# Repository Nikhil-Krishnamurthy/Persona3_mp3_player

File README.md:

# Persona3_mp3_player
A persona 3 style mp3 player with headphone and bluetooth support.

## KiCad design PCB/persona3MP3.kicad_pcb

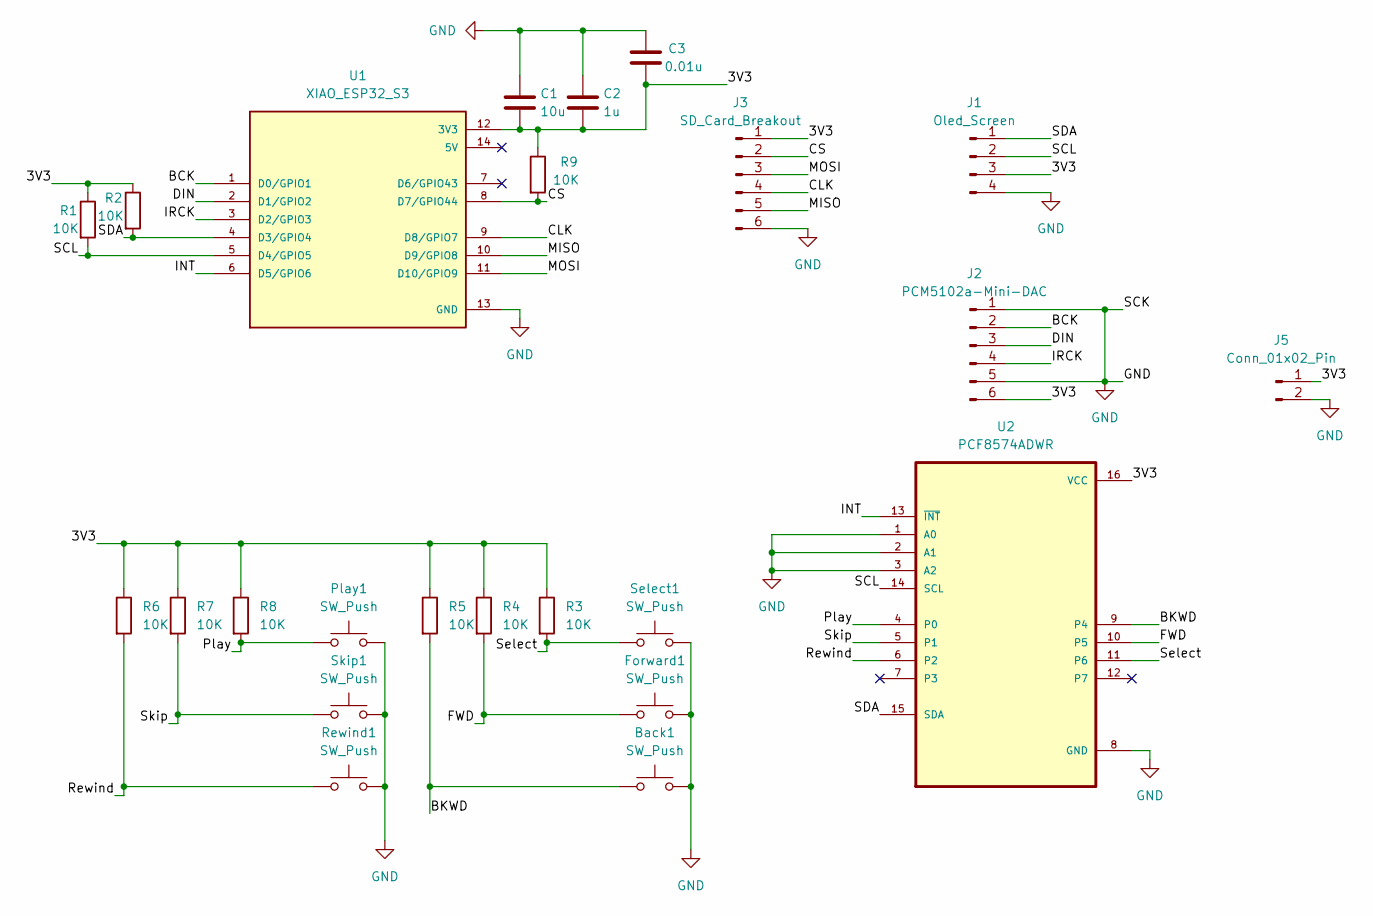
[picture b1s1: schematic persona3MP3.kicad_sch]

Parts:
Back1: SW_Push; PTS645VL392LFS
C1: 10u; C_0805_2012Metric_Pad1.18x1.45mm_HandSolder
C2: 1u; C_0805_2012Metric_Pad1.18x1.45mm_HandSolder
C3: 0.01u; C_0805_2012Metric_Pad1.18x1.45mm_HandSolder
Forward1: SW_Push; PTS645VL392LFS
J1: Oled_Screen; PinHeader_1x04_P2.54mm_Vertical
J2: PCM5102a-Mini-DAC; PinHeader_1x06_P2.54mm_Vertical
J3: SD_Card_Breakout; PinHeader_1x06_P2.54mm_Vertical
J5: Conn_01x02_Pin; PinSocket_1x02_P2.54mm_Vertical
Play1: SW_Push; PTS645VL392LFS
R1, R2, R3, R4, R5, R6, R7, R8, R9: 10K; R_0805_2012Metric_Pad1.20x1.40mm_HandSolder
Rewind1: SW_Push; PTS645VL392LFS
Select1: SW_Push; PTS645VL392LFS
Skip1: SW_Push; PTS645VL392LFS
U1: XIAO_ESP32_S3; MODULE_XIAO_ESP32_S3; PARTREV April 22nd, 2026
U2: PCF8574ADWR; SOIC127P1030X265-16N; DigiKey_Part_Number 296-13105-1-ND

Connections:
/3V3: C1.2, C2.2, C3.2, J1.3, J2.6, J3.1, J5.1, R1.1, R2.1, R3.1, R4.1, R5.1, R6.1, R7.1, R8.1, R9.1, U1.12 (3V3), U2.16 (VCC)
/BCK: J2.2, U1.1 (D0/GPIO1)
/BKWD: Back1.1, R5.2, U2.9 (P4)
/CLK: J3.4, U1.9 (D8/GPIO7)
/CS: J3.2, R9.2, U1.8 (D7/GPIO44)
/DIN: J2.3, U1.2 (D1/GPIO2)
/FWD: Forward1.1, R4.2, U2.10 (P5)
/INT: U1.6 (D5/GPIO6), U2.13 (~INT)
/IRCK: J2.4, U1.3 (D2/GPIO3)
/MISO: J3.5, U1.10 (D9/GPIO8)
/MOSI: J3.3, U1.11 (D10/GPIO9)
/Play: Play1.1, R8.2, U2.4 (P0)
/Rewind: R6.2, Rewind1.1, U2.6 (P2)
/SCL: J1.2, R1.2, U1.5 (D4/GPIO5), U2.14 (SCL)
/SDA: J1.1, R2.2, U1.4 (D3/GPIO4), U2.15 (SDA)
/Select: R3.2, Select1.1, U2.11 (P6)
/Skip: R7.2, Skip1.1, U2.5 (P1)
GND: Back1.2, C1.1, C2.1, C3.1, Forward1.2, J1.4, J2.1, J2.5, J3.6, J5.2, Play1.2, Rewind1.2, Select1.2, Skip1.2, U1.13 (GND), U2.1 (A0), U2.2 (A1), U2.3 (A2), U2.8 (GND)

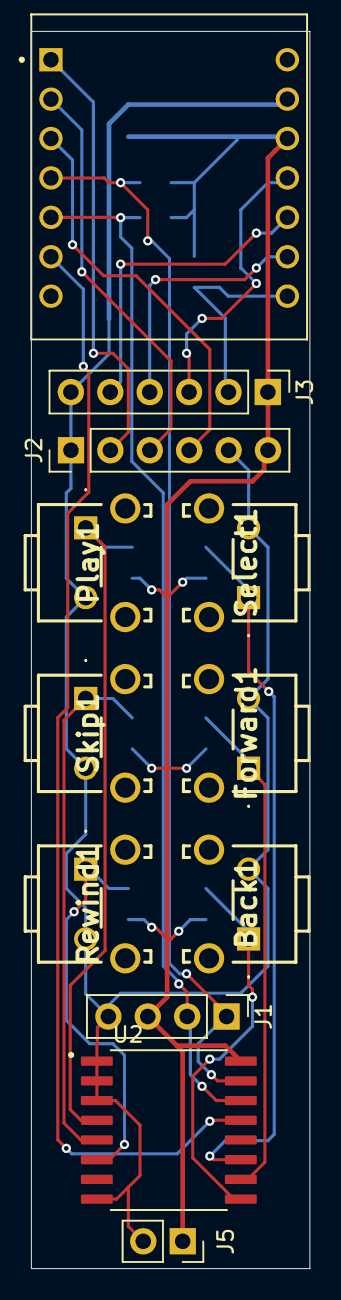
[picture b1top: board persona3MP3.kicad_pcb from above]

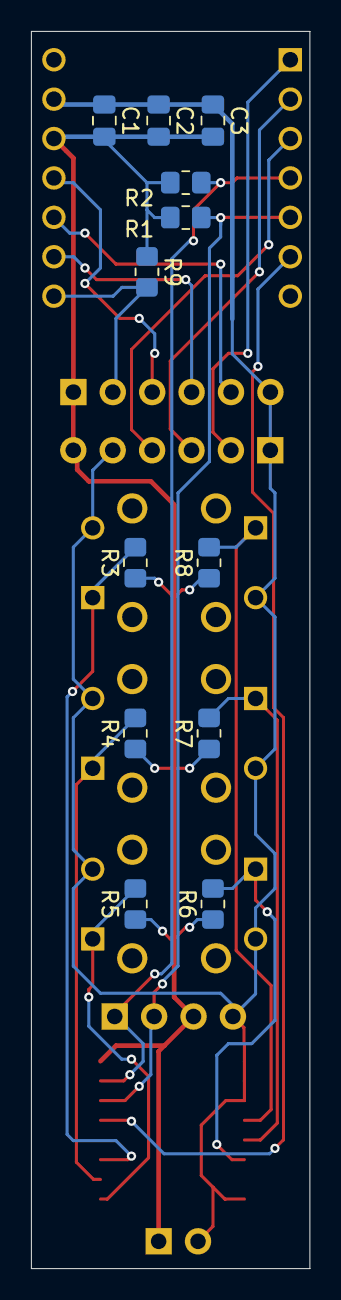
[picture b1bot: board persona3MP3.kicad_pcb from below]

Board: 2 copper layers, 18.0 x 79.8 mm, 24 parts (12 on the bottom side), 18 nets.
